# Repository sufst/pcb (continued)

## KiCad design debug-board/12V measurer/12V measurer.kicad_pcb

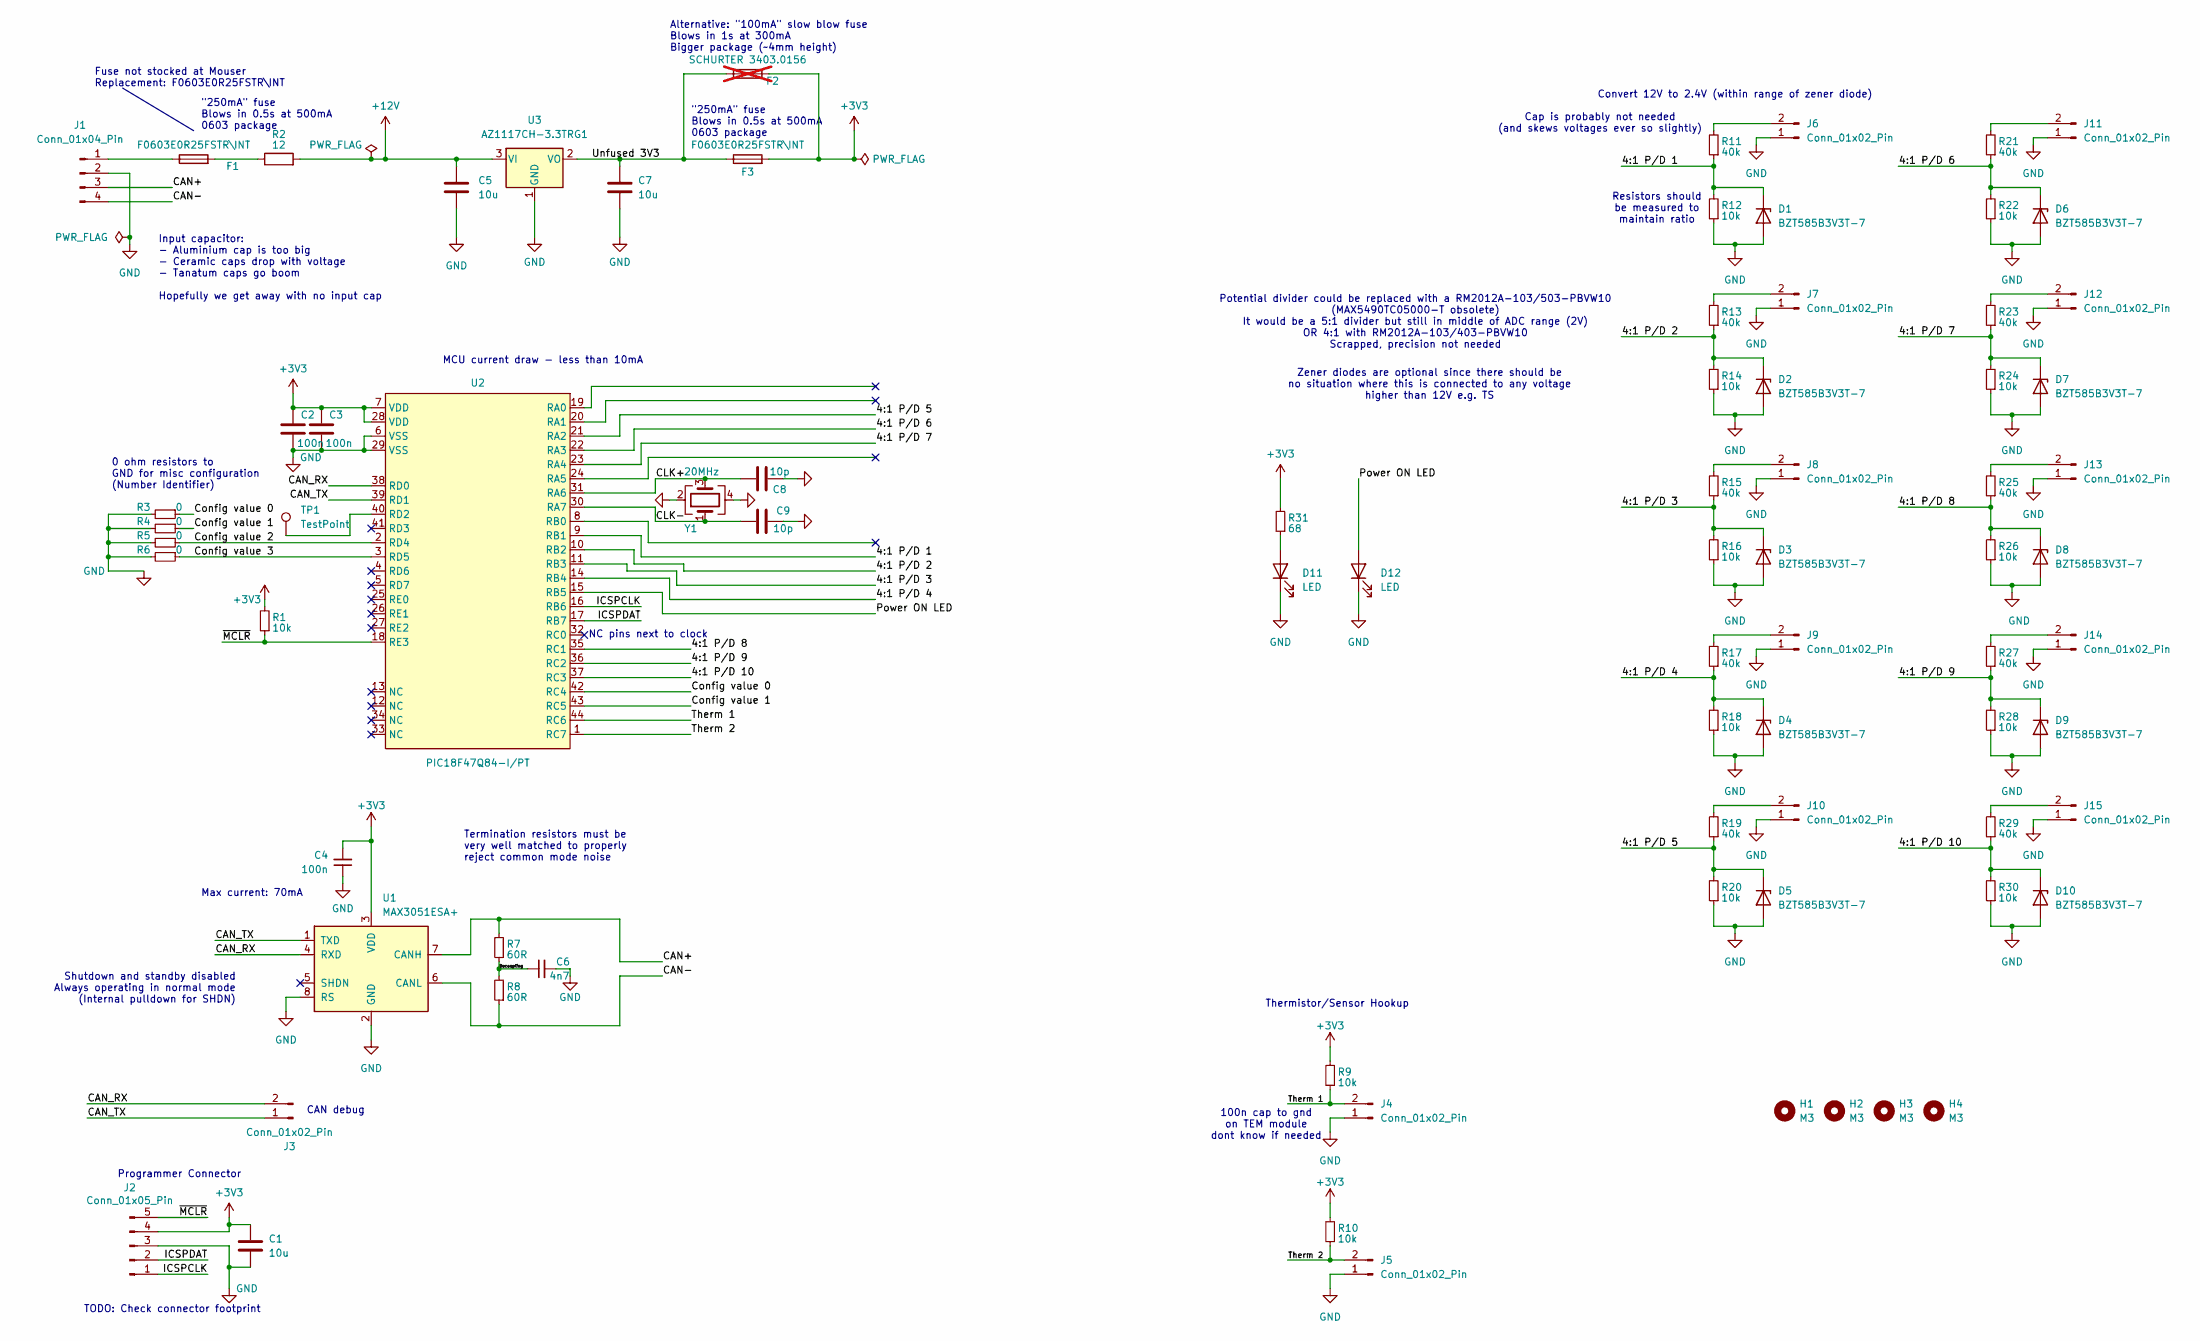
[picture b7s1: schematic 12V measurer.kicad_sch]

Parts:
C1, C5, C7: 10u; C_0805_2012Metric_Pad1.18x1.45mm_HandSolder; Manufacturer_Part_Number GRT21BC71E106KE13L; Mouser Part Number 81-GRT21BC71E106KE13
C2, C3, C4: 100n; C_0805_2012Metric_Pad1.18x1.45mm_HandSolder; Manufacturer_Part_Number KAM21BR71H104JM; Mouser Part Number 581-KAM21BR71H104JM
C6: 4n7; C_0805_2012Metric_Pad1.18x1.45mm_HandSolder; Manufacturer_Part_Number KAM21BR71H472KM; Mouser Part Number 581-KAM21BR71H472KM
C8, C9: 10p; C_0603_1608Metric_Pad1.08x0.95mm_HandSolder; Manufacturer_Part_Number C0805C100J1RACAUTO; Mouser Part Number 80-C0805C100J1RAUTO
D1, D2, D3, D4, D5, D6, D7, D8, D9, D10: BZT585B3V3T-7; D_SOD-523; Mouser Part Number 621-BZT585B3V3T-7
D11: LED; LED_0603_1608Metric_Pad1.05x0.95mm_HandSolder; Mouser Part Number 720-P412P1R258A8J802
D12: LED; LED_0603_1608Metric_Pad1.05x0.95mm_HandSolder; Mouser Part Number 710-150060GS55040
F1, F3: F0603E0R25FSTR\INT; Fuse_0603_1608Metric_Pad1.05x0.95mm_HandSolder; Manufacturer_Part_Number F0603E0R25FSTR\INT; Mouser Part Number 581-F0603E0R25FSTRIN
F2: SCHURTER 3403.0156; Fuse_Schurter_UMT250; not fitted
H1, H2, H3, H4: M3; MountingHole_3.2mm_M3
J1: Conn_01x04_Pin; Molex_Micro-Fit_3.0_43650-0400_1x04_P3.00mm_Horizontal; Manufacturer_Part_Number 43650-0400; Mouser Part Number 538-43650-0400
J2: Conn_01x05_Pin; PinHeader_1x05_P2.54mm_Vertical; Manufacturer_Part_Number 5-146282-5; Mouser Part Number 571-5-146282-5
J3: Conn_01x02_Pin; Conn2_SMD
J4, J5, J6, J7, J8, J9, J10, J11, J12, J13, J14, J15: Conn_01x02_Pin; Molex_Micro-Fit_3.0_43045-0200_2x01_P3.00mm_Horizontal; Manufacturer_Part_Number 43045-0200; Mouser Part Number 538-43045-0200
R1, R9, R10, R12, R14, R16, R18, R20, R22, R24, R26, R28, R30: 10k; R_0805_2012Metric_Pad1.20x1.40mm_HandSolder; Manufacturer_Part_Number CRGH0805F12R; Mouser Part Number 279-CRGH0805F12R
R2: 12; R_0805_2012Metric_Pad1.20x1.40mm_HandSolder; Manufacturer_Part_Number CRCW080512R0FKEAHP; Mouser Part Number 71-CRCW080512R0FKEAH
R3, R4, R5, R6: 0; R_0805_2012Metric_Pad1.20x1.40mm_HandSolder; Manufacturer_Part_Number CR0805AJ/-000EAS; Mouser Part Number 652-CR0805AJ/-000EAS
R7, R8: 60R; R_0805_2012Metric_Pad1.20x1.40mm_HandSolder; Manufacturer_Part_Number ERJ-P06D60R4V; Mouser Part Number 667-ERJ-P06D60R4V
R11, R13, R15, R17, R19, R21, R23, R25, R27, R29: 40k; R_0805_2012Metric_Pad1.20x1.40mm_HandSolder; Manufacturer_Part_Number CRCW080540K0FKEA; Mouser Part Number 71-CRCW080540K0FKEA
R31: 68; R_0805_2012Metric_Pad1.20x1.40mm_HandSolder; Manufacturer_Part_Number CRCW080568R0FKEAHP; Mouser Part Number 71-CRCW080568R0FKEAH
TP1: TestPoint; TestPoint_Keystone_5010-5014_Multipurpose
U1: MAX3051ESA+; SOIC-8_3.9x4.9mm_P1.27mm; Manufacturer_Part_Number MAX3051ESA+; Mouser Part Number 700-MAX3051ESA
U2: PIC18F47Q84-I/PT; TQFP-44_10x10mm_P0.8mm; Manufacturer_Part_Number PIC18F47Q84-I/PT; Mouser Part Number 579-PIC18F47Q84-I/PT
U3: AZ1117CH-3.3TRG1; SOT-223-3_TabPin2; Manufacturer_Part_Number AZ1117CH-3.3TRG1; Mouser Part Number 621-AZ1117CH-3.3TRG1
Y1: 20MHz; Crystal_SMD_SeikoEpson_FA128-4Pin_2.0x1.6mm; Manufacturer_Part_Number FA-128 20.00M-A0AAYYG80RE0; Mouser Part Number 732-FA12820A0AAYYG80

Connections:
+3V3: C1.1, C2.1, C3.1, C4.2, F2.2, F3.2, J2.4, R1.2, R9.2, R10.2, R31.2, U1.3 (VDD), U2.7 (VDD), U2.28 (VDD)
+12V: C5.1, R2.2, U3.3 (VI)
/4:1 P/D 1: D1.1 (K), R11.1, R12.2, U2.9 (RB1)
/4:1 P/D 2: D2.1 (K), R13.1, R14.2, U2.10 (RB2)
/4:1 P/D 3: D3.1 (K), R15.1, R16.2, U2.11 (RB3)
/4:1 P/D 4: D4.1 (K), R17.1, R18.2, U2.14 (RB4)
/4:1 P/D 5: D5.1 (K), R19.1, R20.2, U2.21 (RA2)
/4:1 P/D 6: D6.1 (K), R21.1, R22.2, U2.22 (RA3)
/4:1 P/D 7: D7.1 (K), R23.1, R24.2, U2.23 (RA4)
/4:1 P/D 8: D8.1 (K), R25.1, R26.2, U2.35 (RC1)
/4:1 P/D 9: D9.1 (K), R27.1, R28.2, U2.36 (RC2)
/4:1 P/D 10: D10.1 (K), R29.1, R30.2, U2.37 (RC3)
/CAN+: J1.3, R7.2, U1.7 (CANH)
/CAN-: J1.4, R8.1, U1.6 (CANL)
/CAN_RX: J3.2, U1.4 (RXD), U2.38 (RD0)
/CAN_TX: J3.1, U1.1 (TXD), U2.39 (RD1)
/CLK+: C8.1, U2.31 (RA6), Y1.3
/CLK-: C9.1, U2.30 (RA7), Y1.1
/Config value 0: R3.1, U2.42 (RC4)
/Config value 1: R4.1, U2.43 (RC5)
/Config value 2: R5.1, U2.2 (RD4)
/Config value 3: R6.1, U2.3 (RD5)
/Decoupling: C6.1, R7.1, R8.2
/ICSPCLK: J2.1, U2.16 (RB6)
/ICSPDAT: J2.2, U2.17 (RB7)
/Power ON LED: D12.2 (A), U2.15 (RB5)
/Therm 1: J4.2, R9.1, U2.44 (RC6)
/Therm 2: J5.2, R10.1, U2.1 (RC7)
/Unfused 3V3: C7.1, F2.1, F3.1, U3.2 (VO)
/~MCLR: J2.5, R1.1, U2.18 (RE3)
GND: C1.2, C2.2, C3.2, C4.1, C5.2, C6.2, C7.2, C8.2, C9.2, D1.2 (A), D2.2 (A), D3.2 (A), D4.2 (A), D5.2 (A), D6.2 (A), D7.2 (A), D8.2 (A), D9.2 (A), D10.2 (A), D11.1 (K), D12.1 (K), J1.2, J2.3, J4.1, J5.1, J6.1, J7.1, J8.1, J9.1, J10.1, J11.1, J12.1, J13.1, J14.1, J15.1, R3.2, R4.2, R5.2, R6.2, R12.1, R14.1, R16.1, R18.1, R20.1, R22.1, R24.1, R26.1, R28.1, R30.1, U1.2 (GND), U1.8 (RS), U2.6 (VSS), U2.29 (VSS), U3.1 (GND), Y1.2, Y1.4
unnamed: D11.2 (A), R31.1
unnamed: F1.2, R2.1
unnamed: F1.1, J1.1
unnamed: J6.2, R11.2
unnamed: J7.2, R13.2
unnamed: J8.2, R15.2
unnamed: J9.2, R17.2
unnamed: J10.2, R19.2
unnamed: J11.2, R21.2
unnamed: J12.2, R23.2
unnamed: J13.2, R25.2
unnamed: J14.2, R27.2
unnamed: J15.2, R29.2
unnamed: TP1.1, U2.40 (RD2)

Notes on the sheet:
Input capacitor: - Aluminium cap is too big - Ceramic caps drop with voltage - Tanatum caps go boom Hopefully we get away with no input cap
Shutdown and standby disabled Always operating in normal mode (Internal pulldown for SHDN)
Potential divider could be replaced with a RM2012A-103/503-PBVW10 (MAX5490TC05000-T obsolete) It would be a 5:1 divider but still in middle of ADC range (2V) OR 4:1 with RM2012A-103/403-PBVW10 Scrapped, precision not needed
Cap is probably not needed (and skews voltages ever so slightly)
Max current: 70mA
"250mA" fuse Blows in 0.5s at 500mA 0603 package
Termination resistors must be very well matched to properly reject common mode noise
TODO: Check connector footprint
Fuse not stocked at Mouser Replacement: F0603E0R25FSTR\INT
Zener diodes are optional since there should be no situation where this is connected to any voltage higher than 12V e.g. TS
Convert 12V to 2.4V (within range of zener diode)
NC pins next to clock
0 ohm resistors to GND for misc configuration (Number Identifier)
100n cap to gnd on TEM module dont know if needed
MCU current draw - less than 10mA
CAN debug
Resistors should be measured to maintain ratio
Programmer Connector
Alternative: "100mA" slow blow fuse Blows in 1s at 300mA Bigger package (~4mm height)
Thermistor/Sensor Hookup

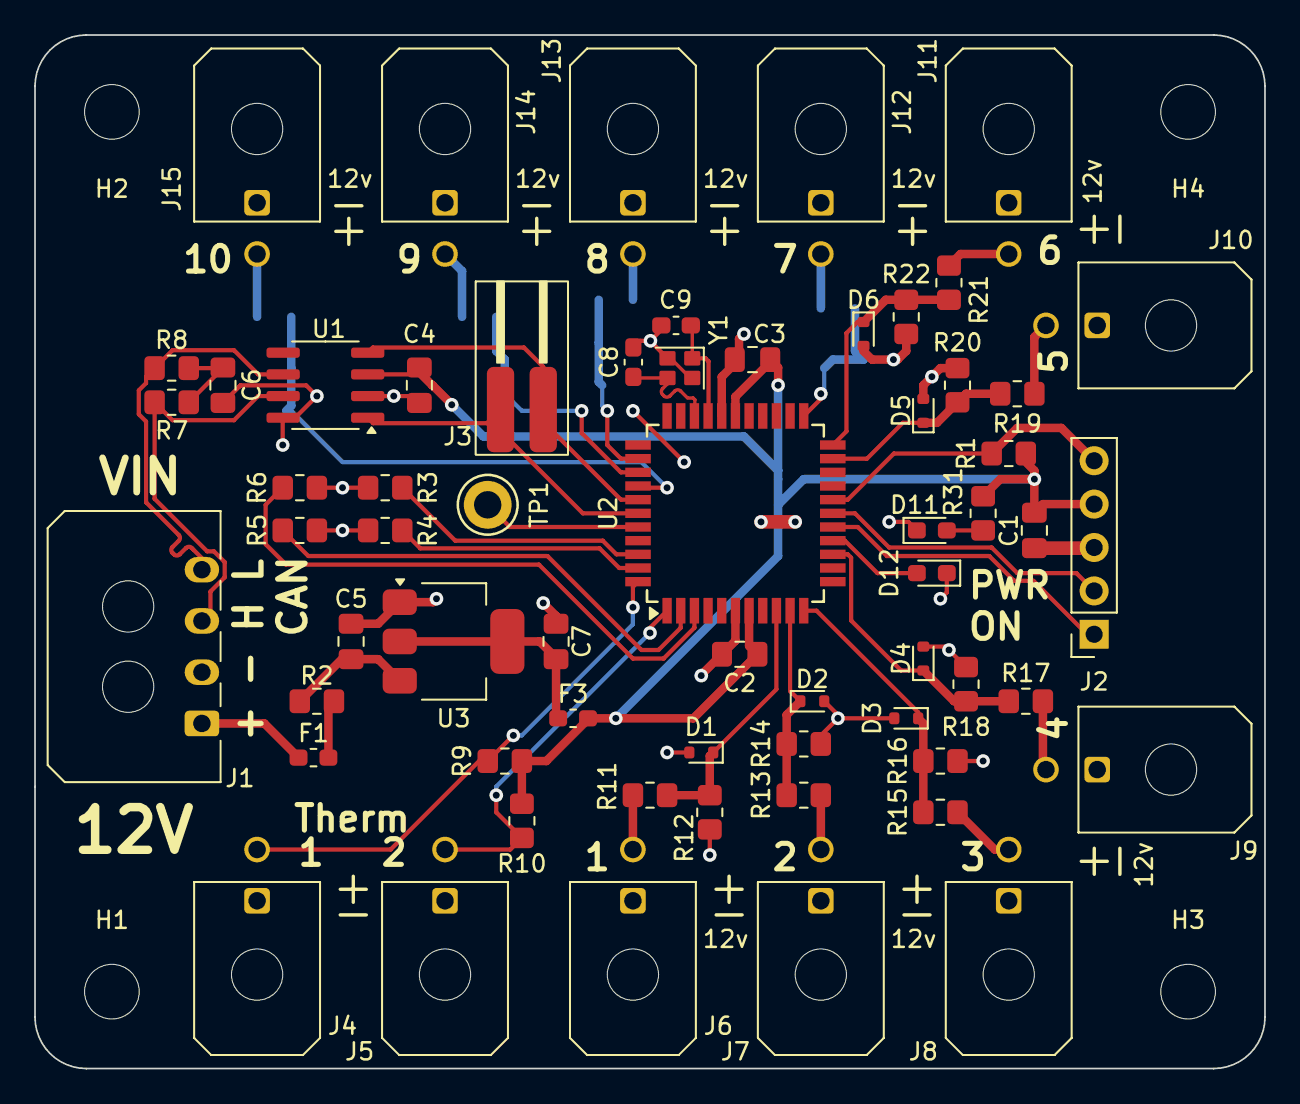
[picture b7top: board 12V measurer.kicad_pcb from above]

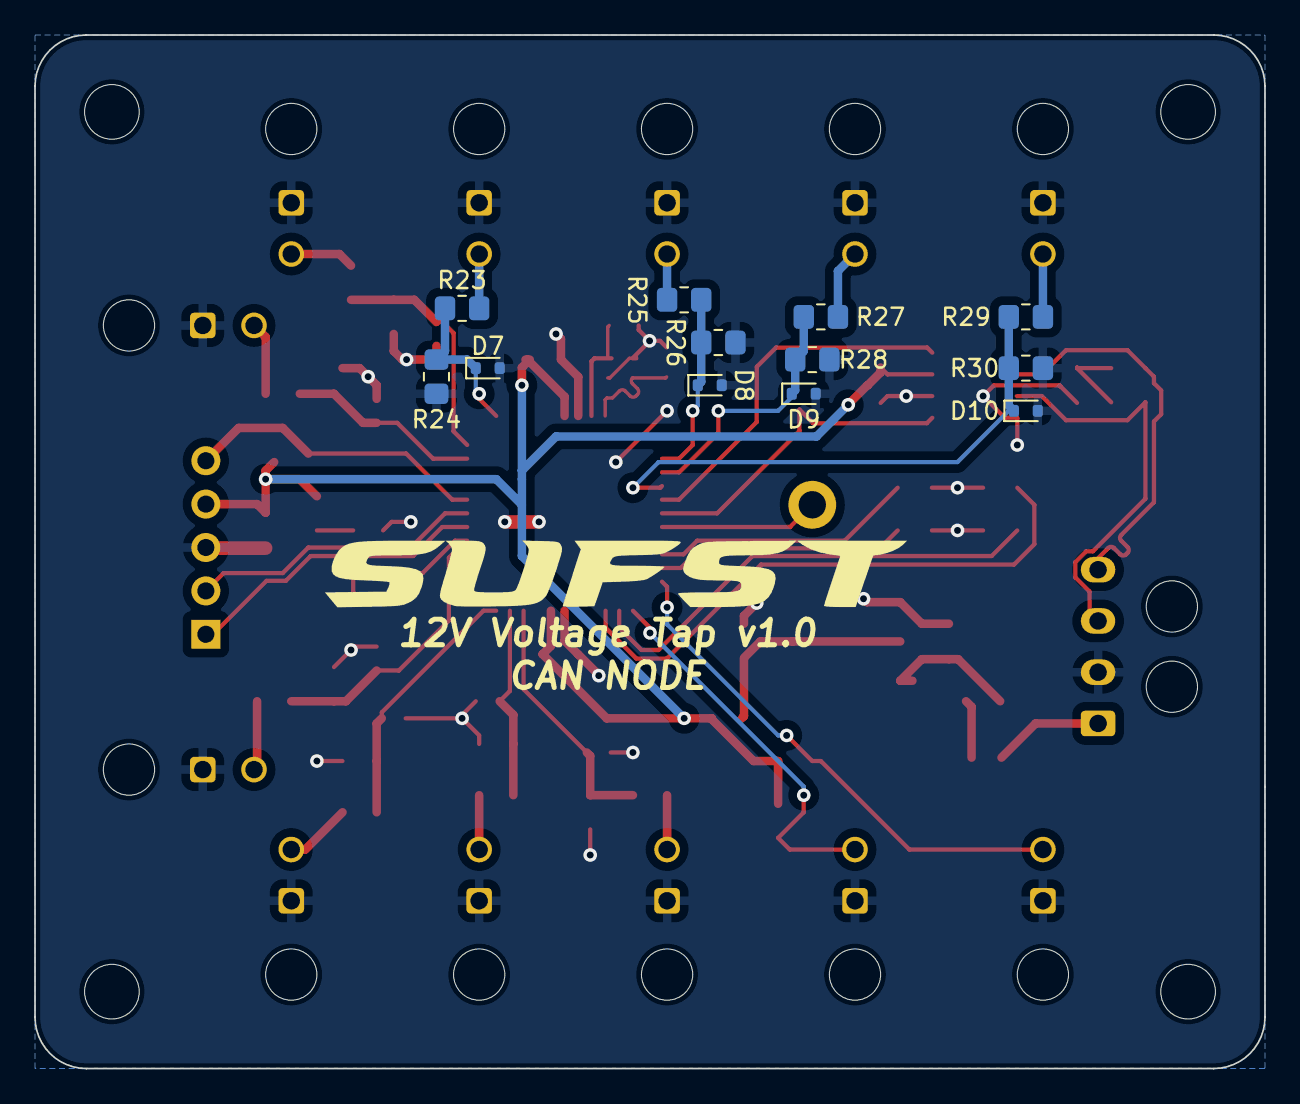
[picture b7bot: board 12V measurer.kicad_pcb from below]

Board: 2 copper layers, 72.0 x 60.5 mm, 78 parts (12 on the bottom side), 45 nets.
